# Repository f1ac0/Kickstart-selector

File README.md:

# Kickstart selector
Use a 1MB 27C800 or 2MB 27C160 ROM chip prepared with 2 or 4 kickstart images, select which one to boot your Amiga from.

You may also configure the board to use a 27C322 and 8 kickstart images, or 1MB kickstarts.

# Disclaimer
This is a hobbyist project, it comes with no warranty and no support. Also remember that the Amiga machines are about 30 years old and may fail because of such hardware expansions.

I publish this work using the CC-BY-NC-SA license.

If you find it useful and want to reward me : I am always looking for Amiga/Amstrad CPC hardware to repair and hack, please contact me.

# Making it
Check for shorts at least between 5V and GND traces before applying power !

- Use a socket /pin header with long enough pins that will connect to the computer socket through the PCB. I use pins taken from a round pin header strip
- Install R1 and R2. Leave RN unpopulated unless you know what you are doing.
- Chop pin 1 and 42 so that it does not make contact with the computer socket
- Install JP1 and JPN

## 1MB kickstarts
- Do NOT install R1
- Do NOT chop pin 1 
- Do NOT install JP1

## A500 Rev5 BUG
There is a bug on A500 Rev5 motherboards where the address line A17 is not routed to Pin 1 of its 40 socket but to Pin 31 instead (Byte/A20 of our EPROM). It affects operation of 512K kickstarts.
 1. Close JP4 : this connects Pins 1 and 31 of the computer socket
 2. Insulate the BYTE pin of the Eprom : Bend Pin 31 of the Eprom and connect it to Pin 22 (VCC, Pull-up to keep the EPROM in 16 bit mode).
 3. Do NEVER close JP3 ! That would cause a short between VCC and GND.
WARNING : never install the board in a computer not affected by the bug !

## SUPPORT FOR 27C322 AND 8 BANKS
 1. VERY IMPORTANT : chop the lead of the BYTE Pin 32 so that it does not make contact with the computer socket at any cost
 2. Install R3 and header JP3
If you need to install another type of ROM, then just leave JP3 open.

WARNING : to prevent making shorts between VCC and GND, never install header JP3 while the BYTE pin has not been removed.

# Using it
- Remove the ROM from the motherboard
- Burn and insert the UVPROM on the selector
- Insert the selector in the ROM socket of the motherboard. Make sure it does not pop out during operation.
- Close/open JP1, JP2 and JP3 accordingly
- Turn on the Amiga

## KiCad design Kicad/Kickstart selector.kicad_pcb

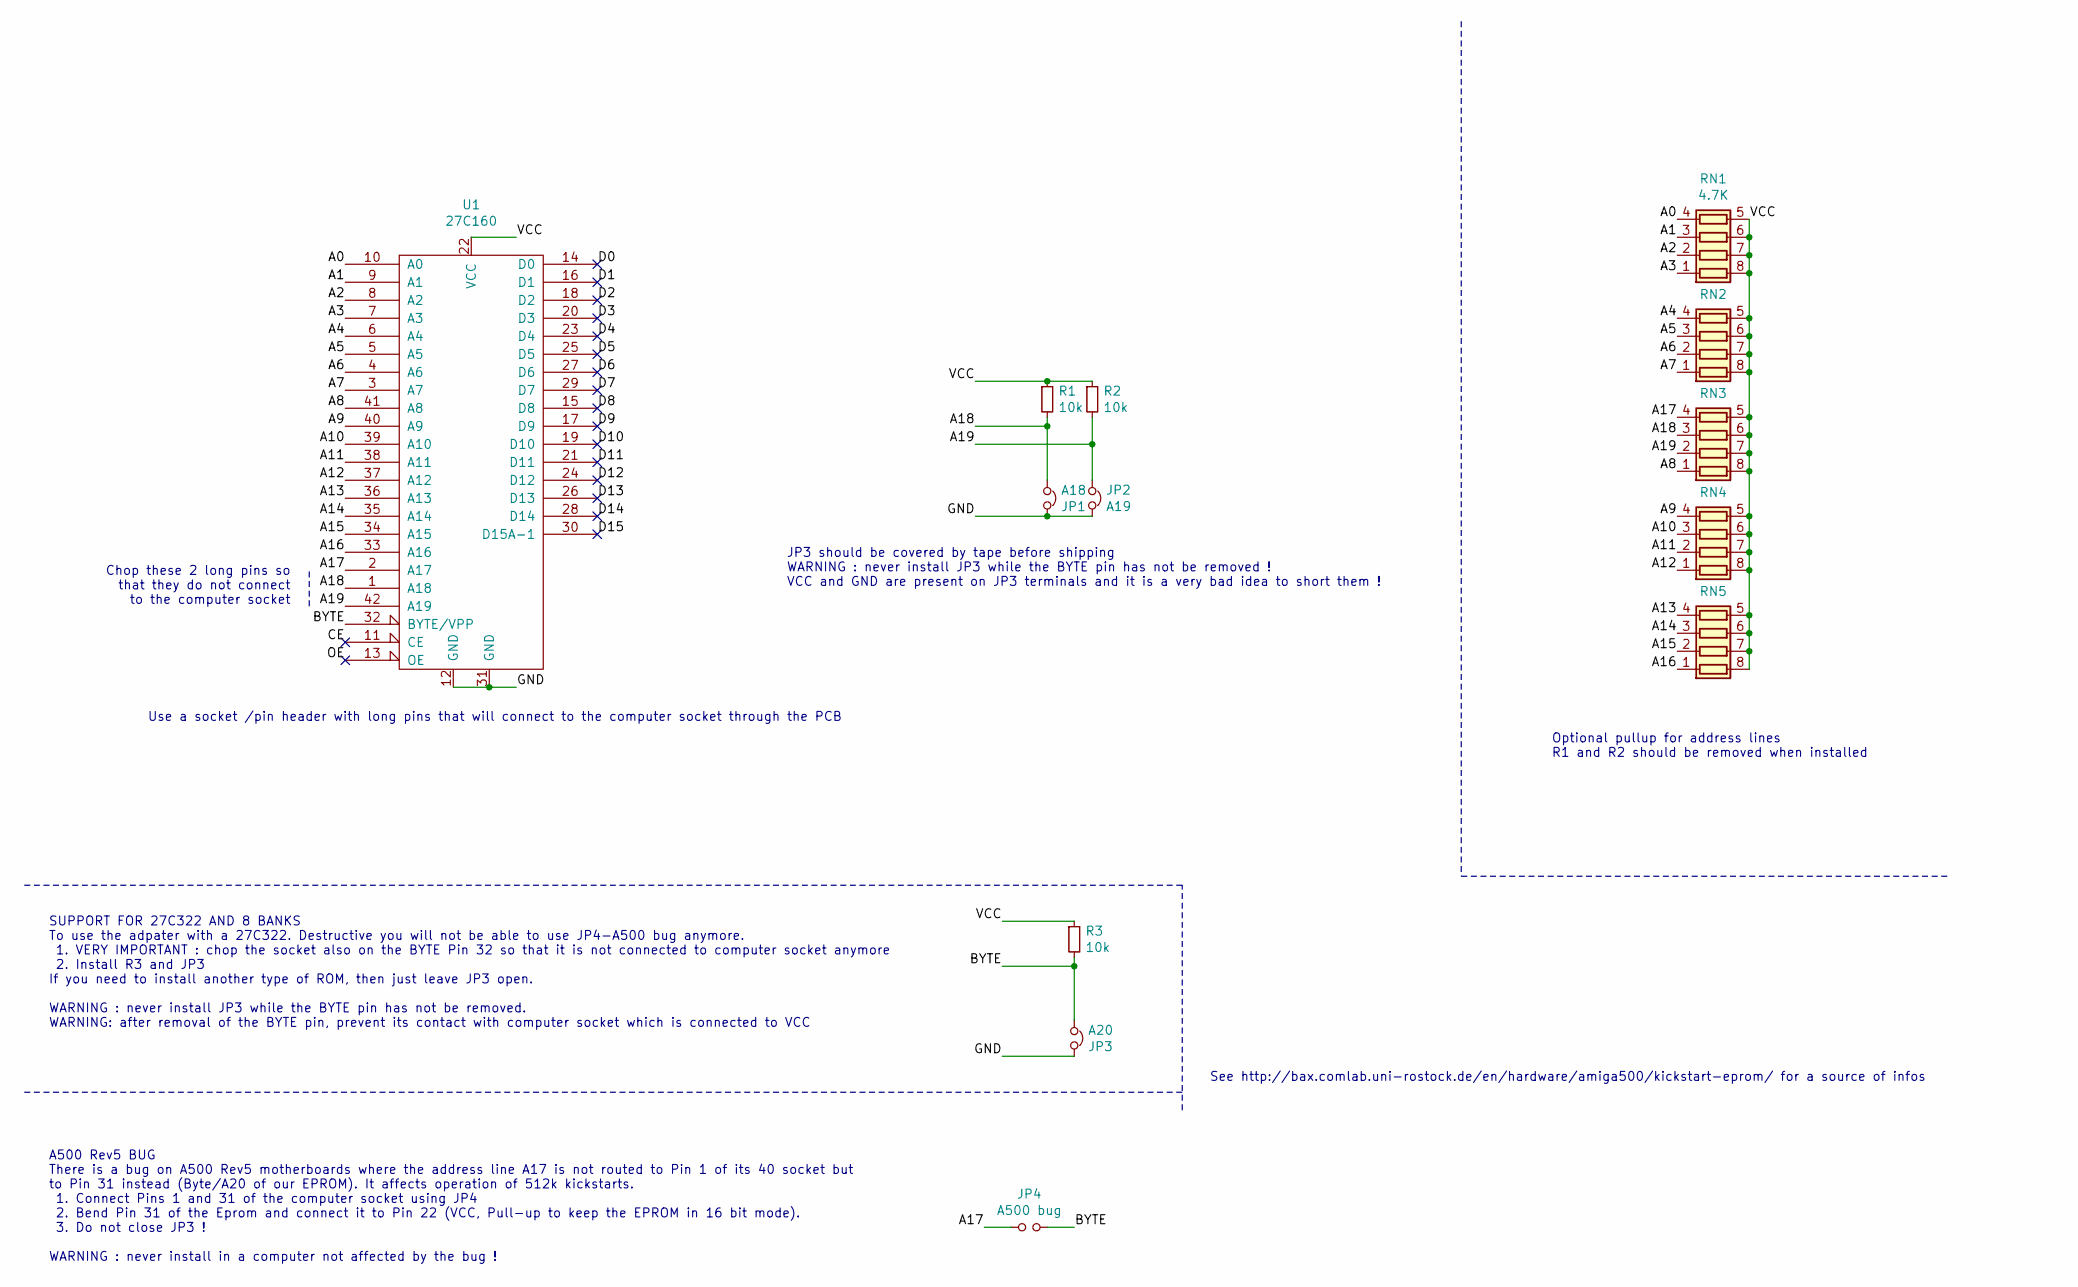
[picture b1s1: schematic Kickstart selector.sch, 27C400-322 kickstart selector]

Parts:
JP1: A18; Pin_Header_1x2_EdgeMount_Pitch2.54mm
JP2: A19; Pin_Header_1x2_EdgeMount_Pitch2.54mm
JP3: A20; Pin_Header_1x2_EdgeMount_Pitch2.54mm
JP4: A500 bug; SOLDER-JUMPER_1-WAY-CLOSED
R1, R2, R3: 10k; R_0805_HandSoldering
RN1, RN2, RN3, RN4, RN5: 4.7K; R_Array_Convex_4x0603
U1: 27C160; DIP-42_W15.24mm

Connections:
/A0: RN1.4 (R4.1), U1.10 (A0)
/A1: RN1.3 (R3.1), U1.9 (A1)
/A2: RN1.2 (R2.1), U1.8 (A2)
/A3: RN1.1 (R1.1), U1.7 (A3)
/A4: RN2.4 (R4.1), U1.6 (A4)
/A5: RN2.3 (R3.1), U1.5 (A5)
/A6: RN2.2 (R2.1), U1.4 (A6)
/A7: RN2.1 (R1.1), U1.3 (A7)
/A8: RN3.1 (R1.1), U1.41 (A8)
/A9: RN4.4 (R4.1), U1.40 (A9)
/A10: RN4.3 (R3.1), U1.39 (A10)
/A11: RN4.2 (R2.1), U1.38 (A11)
/A12: RN4.1 (R1.1), U1.37 (A12)
/A13: RN5.4 (R4.1), U1.36 (A13)
/A14: RN5.3 (R3.1), U1.35 (A14)
/A15: RN5.2 (R2.1), U1.34 (A15)
/A16: RN5.1 (R1.1), U1.33 (A16)
/A17: JP4.1, RN3.4 (R4.1), U1.2 (A17)
/A18: JP1.2, R1.2, RN3.3 (R3.1), U1.1 (A18)
/A19: JP2.1, R2.2, RN3.2 (R2.1), U1.42 (A19)
/BYTE: JP3.2, JP4.2, R3.2, U1.32 (BYTE/VPP)
/CE: U1.11 (CE)
/D0: U1.14 (D0)
/D1: U1.16 (D1)
/D2: U1.18 (D2)
/D3: U1.20 (D3)
/D4: U1.23 (D4)
/D5: U1.25 (D5)
/D6: U1.27 (D6)
/D7: U1.29 (D7)
/D8: U1.15 (D8)
/D9: U1.17 (D9)
/D10: U1.19 (D10)
/D11: U1.21 (D11)
/D12: U1.24 (D12)
/D13: U1.26 (D13)
/D14: U1.28 (D14)
/D15: U1.30 (D15A-1)
/GND: JP1.1, JP2.2, JP3.1, U1.12 (GND), U1.31 (GND)
/OE: U1.13 (OE)
/VCC: R1.1, R2.1, R3.1, RN1.5 (R4.2), RN1.6 (R3.2), RN1.7 (R2.2), RN1.8 (R1.2), RN2.5 (R4.2), RN2.6 (R3.2), RN2.7 (R2.2), RN2.8 (R1.2), RN3.5 (R4.2), RN3.6 (R3.2), RN3.7 (R2.2), RN3.8 (R1.2), RN4.5 (R4.2), RN4.6 (R3.2), RN4.7 (R2.2), RN4.8 (R1.2), RN5.5 (R4.2), RN5.6 (R3.2), RN5.7 (R2.2), RN5.8 (R1.2), U1.22 (VCC)

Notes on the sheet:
Chop these 2 long pins so that they do not connect to the computer socket
Use a socket /pin header with long pins that will connect to the computer socket through the PCB
Optional pullup for address lines R1 and R2 should be removed when installed
See http://bax.comlab.uni-rostock.de/en/hardware/amiga500/kickstart-eprom/ for a source of infos
JP3 should be covered by tape before shipping WARNING : never install JP3 while the BYTE pin has not be removed ! VCC and GND are present on JP3 terminals and it is a very bad idea to short them !
SUPPORT FOR 27C322 AND 8 BANKS To use the adpater with a 27C322. Destructive you will not be able to use JP4-A500 bug anymore. 1. VERY IMPORTANT : chop the socket also on the BYTE Pin 32 so that it is not connected to computer socket anymore 2. Install R3 and JP3 If you need to install another type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
A500 Rev5 BUG There is a bug on A500 Rev5 motherboards where the address line A17 is not routed to Pin 1 of its 40 socket but to Pin 31 instead (Byte/A20 of our EPROM). It affects operation of 512k kickstarts. 1. Connect Pins 1 and 31 of the computer socket using JP4 2. Bend Pin 31 of the Eprom and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

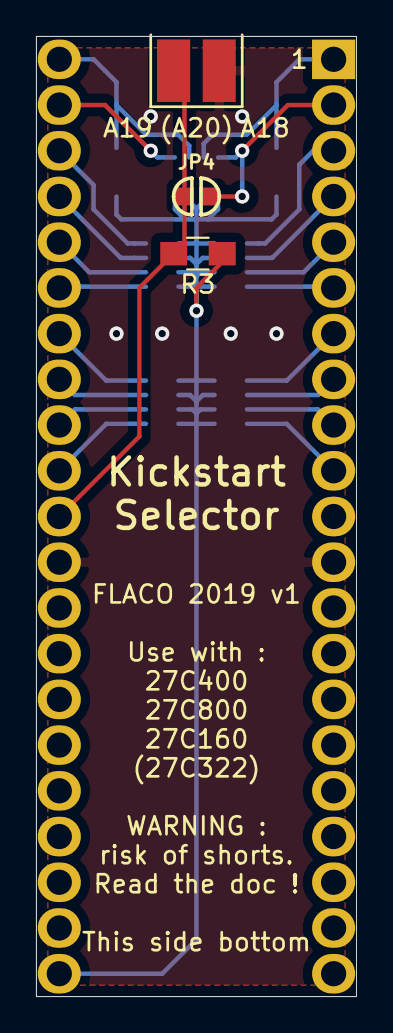
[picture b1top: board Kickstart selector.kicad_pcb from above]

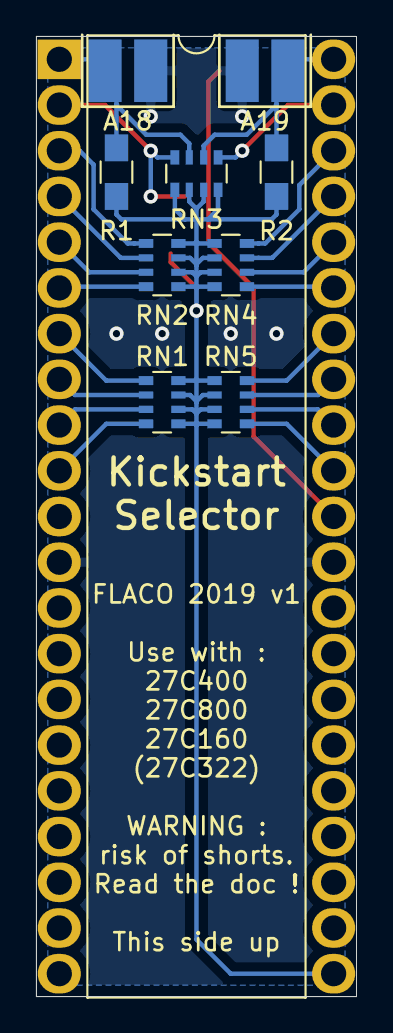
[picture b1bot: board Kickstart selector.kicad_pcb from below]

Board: 2 copper layers, 17.8 x 53.3 mm, 13 parts (10 on the bottom side), 23 nets.

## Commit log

2020-09-07 Respository init with KiCAD files, Readme and License
2022-02-15 Photo and InteractiveHtmlBom

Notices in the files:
Kicad/Kickstart selector.kicad_pcb:
FLACO 2019, licence of this PCB is CC-BY-NC-SA
Kicad/Kickstart selector.sch:
FLACO 2019, licence of this schematic is CC-BY-NC-SA
